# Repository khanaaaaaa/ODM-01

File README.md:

# ODM-01

## Zine

## What It Is & Why I Made It

It is a decorative/ badge-like PCB shaped like the Attack On Titan 'Wings of Freedom' emblem. I honestly wanted to make something anime related, that was fun but also a beginner friendly project. So I made this PCB with my previous knowledge. First I wanted to make the whole PCB like the Attack On Titan badge but that didn't really work out so I opted for something that I had a bit more knowledge of. So, I decided to really embody the badge in the silkscreen.

This board consists of 14 LEDs around the perimeter which I kept for a glowing effect. It is portable as I have added a coin cell battery holder for convinience and to be able to wear it like an actual badge. It has resistors, IC, and also a capacitor for driving the LED. Also consists of a test point to probe voltage during testing and debugging.

## How To Use It

1. Insert a CR2032 coin cell battery into the battery holder at the base, make sure the polarity matches the markings on the board.
2. Once the battery is kept, the circuit powers on automatically and the LEDs will light up.
3. The light sensor will automtically adjust the LEDs based on surrounding brightness.
4. Attach the badge to anything!
5. If the LEDs don't light up, use a multimeter on the test point to check the voltage and identify any soldering issue.

## Schematic

## PCB

## 3d View

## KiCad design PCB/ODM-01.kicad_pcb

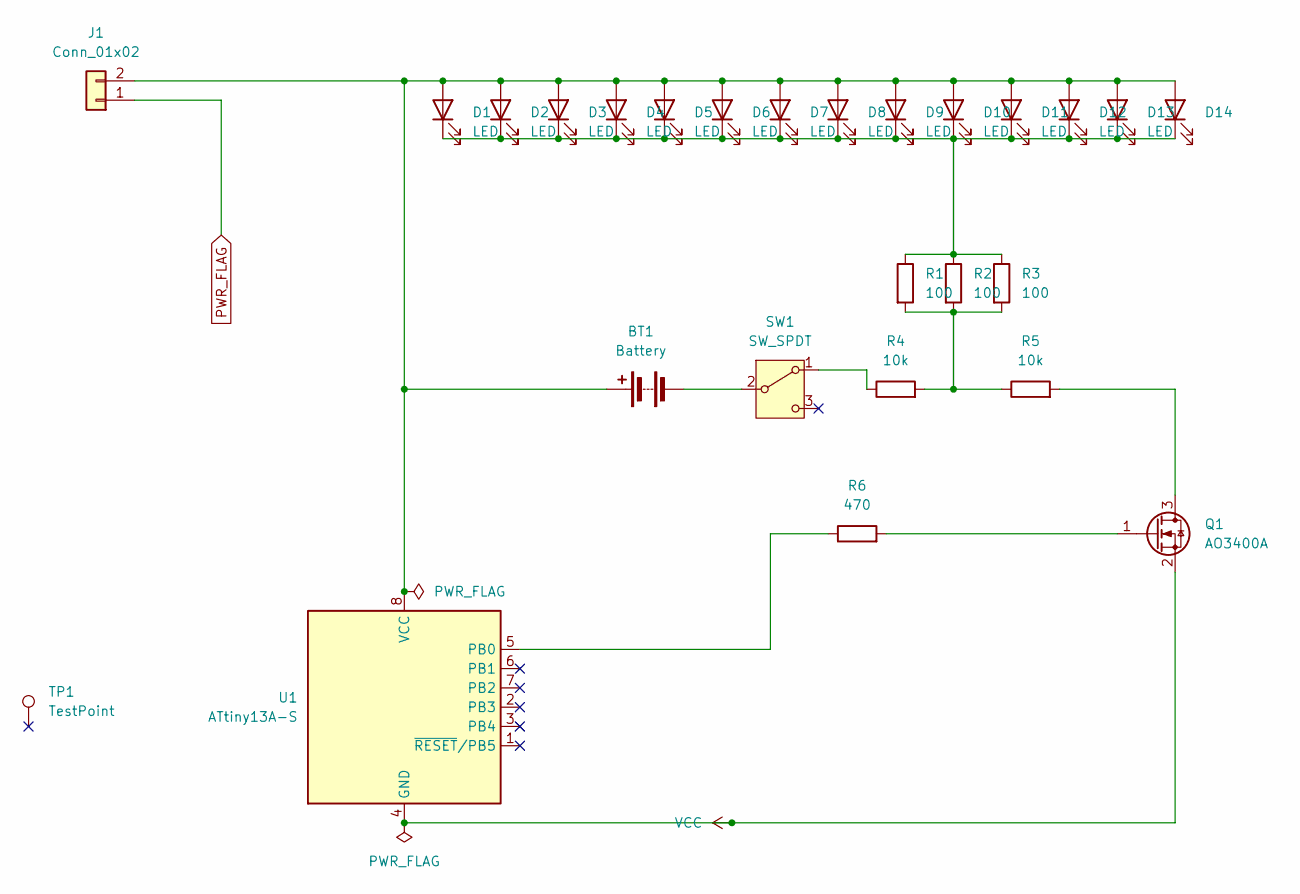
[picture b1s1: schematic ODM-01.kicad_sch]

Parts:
BT1: Battery; BatteryHolder_Keystone_3034_1x20mm
D1, D2, D3, D4, D5, D6, D7, D8, D9, D10, D11, D12, D13, D14: LED; LED_D3.0mm
J1: Conn_01x02; PinHeader_1x02_P2.54mm_Vertical
Q1: AO3400A; SOT-23
R1, R2, R3: 100; R_0805_2012Metric
R4, R5: 10k; R_0805_2012Metric
R6: 470; R_0805_2012Metric
SW1: SW_SPDT; SW_SPDT_PCM12
TP1: TestPoint; TestPoint_Pad_D1.5mm
U1: ATtiny13A-S; SOIC-8_5.3x5.3mm_P1.27mm

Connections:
unnamed: BT1.1 (+), D1.2 (A), D2.2 (A), D3.2 (A), D4.2 (A), D5.2 (A), D6.2 (A), D7.2 (A), D8.2 (A), D9.2 (A), D10.2 (A), D11.2 (A), D12.2 (A), D13.2 (A), D14.2 (A), J1.2, U1.8 (VCC)
unnamed: BT1.2 (-), SW1.2 (B)
unnamed: D1.1 (K), D2.1 (K), D3.1 (K), D4.1 (K), D5.1 (K), D6.1 (K), D7.1 (K), D8.1 (K), D9.1 (K), D10.1 (K), D11.1 (K), D12.1 (K), D13.1 (K), D14.1 (K), R1.1, R2.1, R3.1
unnamed: Q1.3 (D), R5.2
unnamed: Q1.1 (G), R6.2
unnamed: R1.2, R2.2, R3.2, R4.2, R5.1
unnamed: R4.1, SW1.1 (A)
unnamed: R6.1, U1.5 (PB0)
PWR_FLAG: J1.1
VCC: Q1.2 (S), U1.4 (GND)

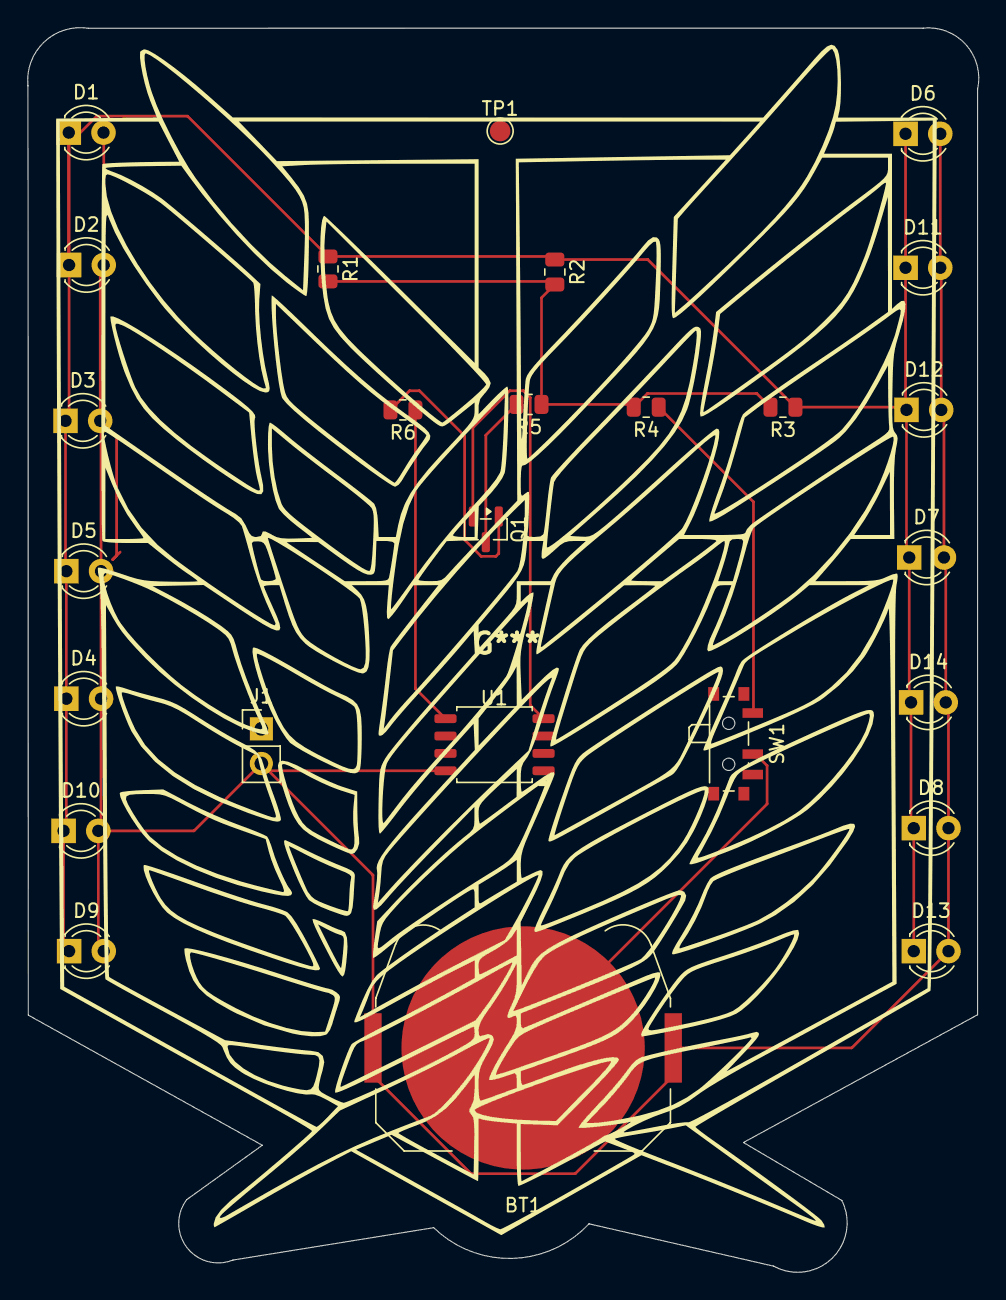
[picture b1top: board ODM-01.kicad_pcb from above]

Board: 2 copper layers, 69.6 x 91.1 mm, 26 parts (0 on the bottom side), 9 nets.

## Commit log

2026-05-16 Added the files of the pcb
2026-05-23 Update README with project details and usage steps
    Added detailed project description and usage instructions.
2026-05-23 Completed the README, added the BOM and organized the files
2026-05-23 BOM links not working, found alternatives
2026-05-26 Update README with image
